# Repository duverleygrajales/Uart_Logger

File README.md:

No Longer Available
Only for Jekyll Probes
Install the jekyll theme in Docs Folder

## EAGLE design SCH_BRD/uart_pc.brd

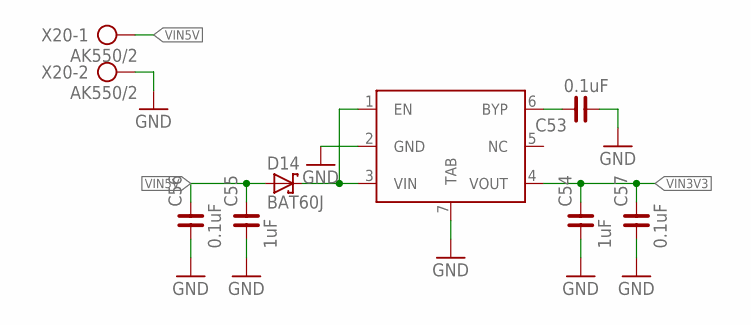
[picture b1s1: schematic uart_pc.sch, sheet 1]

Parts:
C53, C56, C57: 0.1uF; C0603
C54, C55: 1uF; C0603
D14: BAT60J; SOD323_ST
U$3: MIC5353-3.3YMT-TR; DFN-6_DC-L
X20: AK550/2

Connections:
GND: C53.1, C54.1, C55.1, C56.1, C57.1, U$3.2 (GND), U$3.7 (TAB), X20.2; also elsewhere on the board
unnamed: D14.C, U$3.1 (EN), U$3.3 (VIN)
unnamed: C53.2, U$3.6 (BYP)
VIN3V3: C54.2, C57.2, U$3.4 (VOUT); also elsewhere on the board
VIN5V: C55.2, C56.2, D14.A, X20.1; also elsewhere on the board

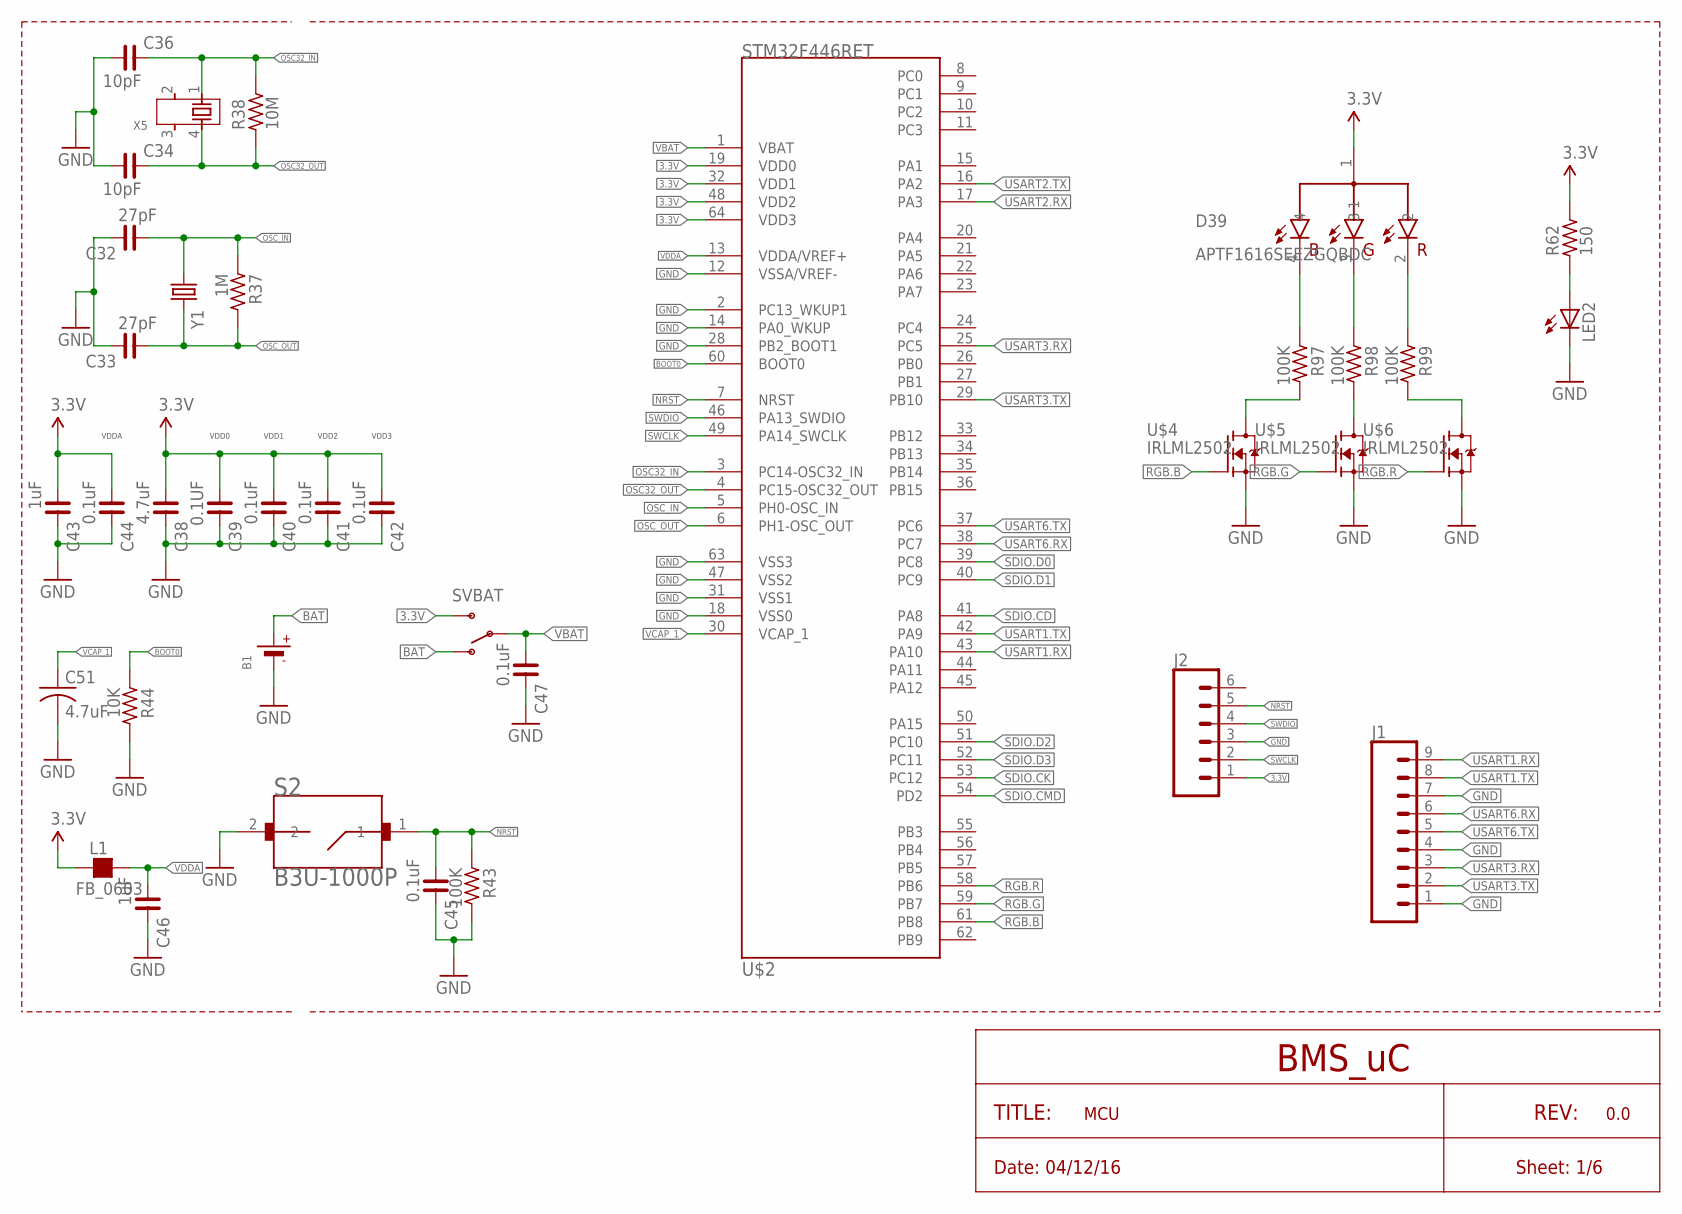
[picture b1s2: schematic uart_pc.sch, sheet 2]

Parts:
B1: BATTERYCR1220_SMT; CR1220
C32, C33: 27pF; C0603
C34, C36: 10pF; C0603
C38: 4.7uF; C0603
C39: 0.1UF; C0603
C40, C41, C42, C44, C45, C47: 0.1uF; C0603
C43, C46: 1uF; C0603
C51: 4.7uF; C1206
D39: APTF1616SEEZGQBDC; 0606(1616)
J1: CONN_09; 1X09
J2: CONN_06SILK_FEMALE_PTH; 1X06
L1: FB_0603; L0603
LED2: LEDCHIP-LED0603; CHIP-LED0603
R37: 1M; R0603
R38: 10M; R0603
R43, R97, R98, R99: 100K; R0603
R44: 10K; R0603
R62: 150; R0603
S2: B3U-1000P; SW_B3U-1000P
SVBAT: SWITCH-SPDTSMD; AYZ0202
U$2: STM32F446RET; LQFP64
U$4, U$5, U$6: IRLML2502; SOT23
X5: CRYSTAL-4PIN; ABRACON-ABS25-32.768KHZ
Y1: CRYSTALSMD; HC49UP

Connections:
3.3V: C38.1, C39.1, C40.1, C41.1, C42.1, C43.1, C44.1, D39.1, J2.1, L1.1, R62.2, SVBAT.3 (S), U$2.19 (VDD0), U$2.32 (VDD1), U$2.48 (VDD2), U$2.64 (VDD3); also elsewhere on the board
BAT: B1.+$1 (+), SVBAT.1 (O)
BOOT0: R44.1, U$2.60 (BOOT0)
GND: B1.-, C32.2, C33.2, C34.1, C36.1, C38.2, C39.2, C40.2, C41.2, C42.2, C43.2, C44.2, C45.2, C46.2, C47.2, C51.2, J1.1, J1.4, J1.7, J2.3, LED2.C, R43.2, R44.2, S2.2, U$2.2 (PC13_WKUP1), U$2.12 (VSSA/VREF-), U$2.14 (PA0_WKUP), U$2.18 (VSS0), U$2.28 (PB2_BOOT1), U$2.31 (VSS1), U$2.47 (VSS2), U$2.63 (VSS3), U$4.2 (S), U$5.2 (S), U$6.2 (S); also elsewhere on the board
unnamed: D39.3, R98.1
unnamed: D39.2, R99.1
unnamed: LED2.A, R62.1
unnamed: D39.4, R97.1
unnamed: R97.2, U$4.3 (D)
unnamed: R98.2, U$5.3 (D)
unnamed: R99.2, U$6.3 (D)
NRST: C45.1, J2.5, R43.1, S2.1, U$2.7 (NRST)
OSC32_IN: C36.2, R38.2, U$2.3 (PC14-OSC32_IN), X5.1
OSC32_OUT: C34.2, R38.1, U$2.4 (PC15-OSC32_OUT), X5.4
OSC_IN: C32.1, R37.1, U$2.5 (PH0-OSC_IN), Y1.1
OSC_OUT: C33.1, R37.2, U$2.6 (PH1-OSC_OUT), Y1.2
RGB.B: U$2.61 (PB8), U$4.1 (G)
RGB.G: U$2.59 (PB7), U$5.1 (G)
RGB.R: U$2.58 (PB6), U$6.1 (G)
SDIO.CD: U$2.41 (PA8); also elsewhere on the board
SDIO.CK: U$2.53 (PC12); also elsewhere on the board
SDIO.CMD: U$2.54 (PD2); also elsewhere on the board
SDIO.D0: U$2.39 (PC8); also elsewhere on the board
SDIO.D1: U$2.40 (PC9); also elsewhere on the board
SDIO.D2: U$2.51 (PC10); also elsewhere on the board
SDIO.D3: U$2.52 (PC11); also elsewhere on the board
SWCLK: J2.2, U$2.49 (PA14_SWCLK)
SWDIO: J2.4, U$2.46 (PA13_SWDIO)
USART1.RX: J1.9, U$2.43 (PA10)
USART1.TX: J1.8, U$2.42 (PA9)
USART2.RX: U$2.17 (PA3); also elsewhere on the board
USART2.TX: U$2.16 (PA2); also elsewhere on the board
USART3.RX: J1.3, U$2.25 (PC5)
USART3.TX: J1.2, U$2.29 (PB10)
USART6.RX: J1.6, U$2.38 (PC7)
USART6.TX: J1.5, U$2.37 (PC6)
VBAT: C47.1, SVBAT.2, U$2.1 (VBAT)
VCAP_1: C51.1, U$2.30 (VCAP_1)
VDDA: C46.1, L1.2, U$2.13 (VDDA/VREF+)

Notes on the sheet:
TITLE:
REV:
Sheet: 1/6
0.0
Date: 04/12/16
MCU
BMS_uC
VDD0
VDD1
VDD2
VDD3
VDDA

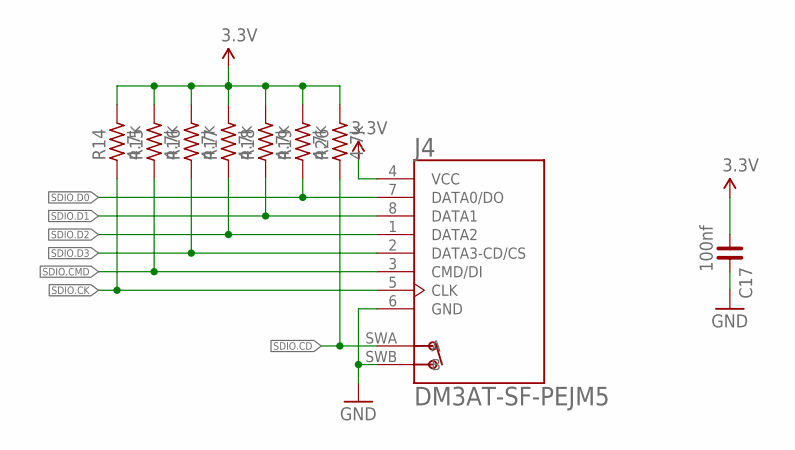
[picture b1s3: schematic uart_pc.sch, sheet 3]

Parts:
C17: 100nf; C0603
J4: DM3AT-SF-PEJM5; HRS_DM3AT-SF-PEJM5
R14, R15, R16, R17, R18, R19, R26: 4.7k; R0603

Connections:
3.3V: C17.1, J4.4 (VCC), R14.2, R15.2, R16.2, R17.2, R18.2, R19.2, R26.2; also elsewhere on the board
GND: C17.2, J4.6 (GND), J4.SWB (B); also elsewhere on the board
SDIO.CD: J4.SWA (A), R26.1; also elsewhere on the board
SDIO.CK: J4.5 (CLK), R14.1; also elsewhere on the board
SDIO.CMD: J4.3 (CMD/DI), R15.1; also elsewhere on the board
SDIO.D0: J4.7 (DATA0/DO), R19.1; also elsewhere on the board
SDIO.D1: J4.8 (DATA1), R18.1; also elsewhere on the board
SDIO.D2: J4.1 (DATA2), R17.1; also elsewhere on the board
SDIO.D3: J4.2 (DATA3-CD/CS), R16.1; also elsewhere on the board

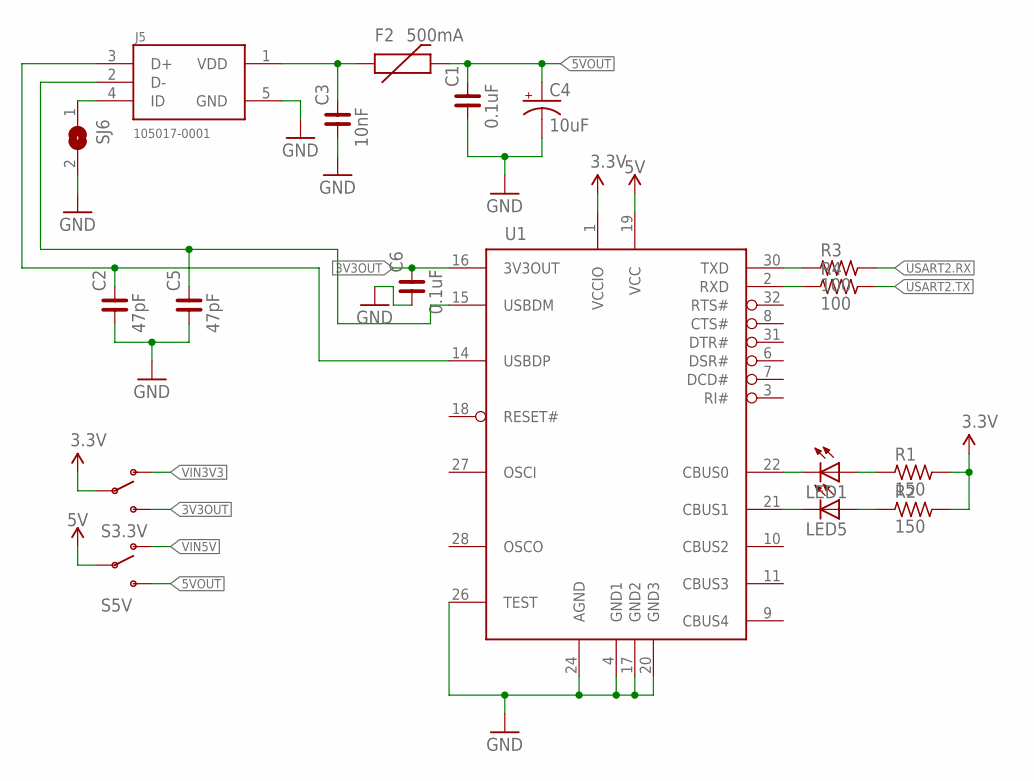
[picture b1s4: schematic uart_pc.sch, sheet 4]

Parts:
C1, C6: 0.1uF; C0603
C2, C5: 47pF; C0603
C3: 10nF; C0603
C4: 10uF; EIA3216
F2: 500mA; PTC-1206
J5: 105017-0001; MOLEX_105017-0001
LED1, LED5: LEDCHIPLED_0603; CHIPLED_0603
R1, R2: 150; R0603
R3, R4: 100; R0603
S3.3V, S5V: SWITCH-SPDTSMD; AYZ0202
SJ6: SOLDERJUMPER; SOLDERJUMPER_ARROW_NOPASTE
U1: FT232RQ; LQFP32

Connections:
3.3V: R1.2, R2.2, S3.3V.2, U1.1 (VCCIO); also elsewhere on the board
3V3OUT: C6.2, S3.3V.3 (S), U1.16 (3V3OUT)
5V: S5V.2, U1.19 (VCC)
5VOUT: C1.2, C4.A (+), F2.2, S5V.3 (S)
GND: C1.1, C2.1, C3.1, C4.C (-), C5.1, C6.1, J5.5 (GND), SJ6.2, U1.4 (GND1), U1.17 (GND2), U1.20 (GND3), U1.24 (AGND), U1.26 (TEST); also elsewhere on the board
unnamed: C5.2, J5.2 (D-), U1.15 (USBDM)
unnamed: C2.2, J5.3 (D+), U1.14 (USBDP)
unnamed: C3.2, F2.1, J5.1 (VDD)
unnamed: J5.4 (ID), SJ6.1
unnamed: LED1.C, U1.22 (CBUS0)
unnamed: LED5.C, U1.21 (CBUS1)
unnamed: LED1.A, R1.1
unnamed: LED5.A, R2.1
unnamed: R3.1, U1.30 (TXD)
unnamed: R4.1, U1.2 (RXD)
USART2.RX: R3.2; also elsewhere on the board
USART2.TX: R4.2; also elsewhere on the board
VIN3V3: S3.3V.1 (O); also elsewhere on the board
VIN5V: S5V.1 (O); also elsewhere on the board

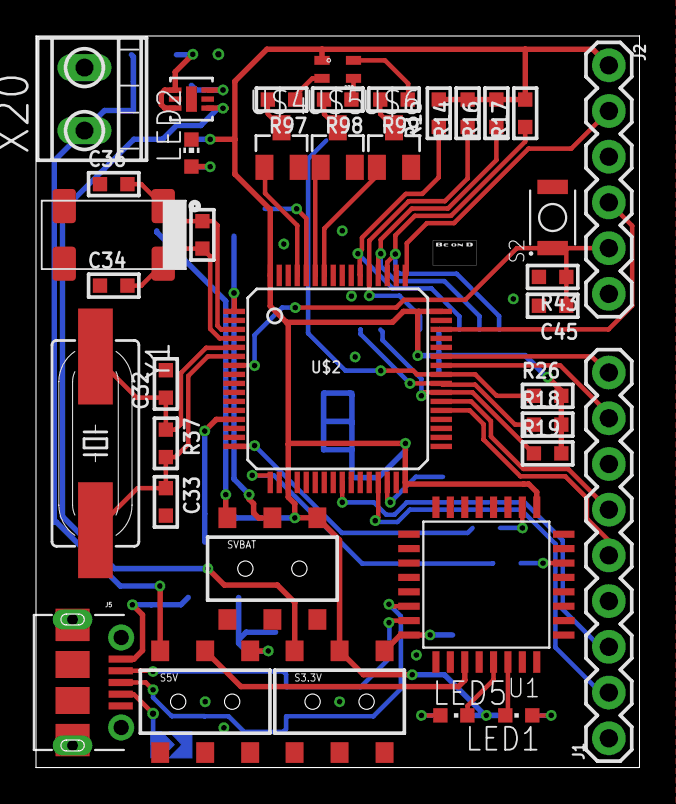
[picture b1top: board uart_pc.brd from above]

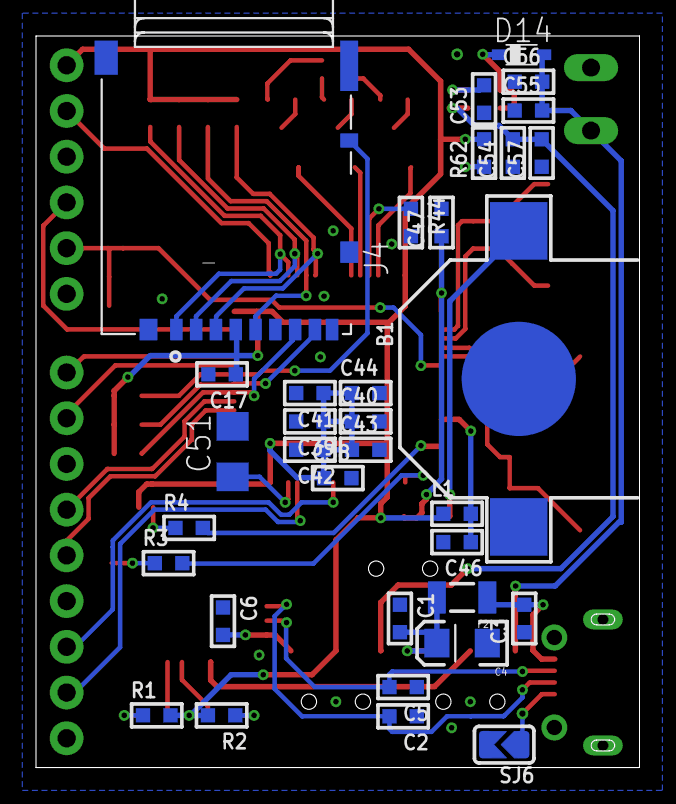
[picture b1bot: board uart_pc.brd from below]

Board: 2 copper layers, 33.5 x 40.6 mm, 72 parts (34 on the bottom side), 56 nets.

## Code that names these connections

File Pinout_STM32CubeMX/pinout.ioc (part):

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Mcu.Name=STM32F446R(C-E)Tx
Mcu.Package=LQFP64
Mcu.UserName=STM32F446RETx
PA10.Mode=Asynchronous
PA10.Signal=USART1_RX
PA2.Mode=Asynchronous
PA2.Signal=USART2_TX
PA3.Mode=Asynchronous
PA3.Signal=USART2_RX
PA8.GPIOParameters=GPIO_Label
PA8.GPIO_Label=Card_Detect
PA8.Signal=GPIO_Input
PA9.Mode=Asynchronous
PA9.Signal=USART1_TX
PB10.Mode=Asynchronous
PB10.Signal=USART3_TX
PB6.Signal=S_TIM4_CH1
PB7.Signal=S_TIM4_CH2
PB8.Signal=S_TIM4_CH3
PC10.Mode=SD_4_bits_Wide_bus
PC10.Signal=SDIO_D2
PC11.Mode=SD_4_bits_Wide_bus
PC11.Signal=SDIO_D3
PC12.Mode=SD_4_bits_Wide_bus
PC12.Signal=SDIO_CK
PC14-OSC32_IN.Mode=LSE-External-Oscillator
PC14-OSC32_IN.Signal=RCC_OSC32_IN
PC15-OSC32_OUT.Mode=LSE-External-Oscillator
PC15-OSC32_OUT.Signal=RCC_OSC32_OUT
PC5.Mode=Asynchronous
PC5.Signal=USART3_RX
PC6.Mode=Asynchronous
PC6.Signal=USART6_TX
PC7.Mode=Asynchronous
PC7.Signal=USART6_RX
PC8.Mode=SD_4_bits_Wide_bus
PC8.Signal=SDIO_D0
PC9.Mode=SD_4_bits_Wide_bus
PC9.Signal=SDIO_D1
PD2.Mode=SD_4_bits_Wide_bus
PD2.Signal=SDIO_CMD
PH0-OSC_IN.Mode=HSE-External-Oscillator
PH0-OSC_IN.Signal=RCC_OSC_IN
PH1-OSC_OUT.Mode=HSE-External-Oscillator
PH1-OSC_OUT.Signal=RCC_OSC_OUT
RCC.HSE_VALUE=8000000
RCC.SYSCLKFreq_VALUE=72000000
RCC.SYSCLKSource=RCC_SYSCLKSOURCE_PLLCLK

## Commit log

2017-09-19 ToDo .brd
    Full .sch we need to finish the board
2017-09-19 Work .brd 19/09/17
2017-09-20 Work .brd 20/09/17
2017-09-21 Finished sch and brd
    Version beta
2018-03-28 Something to commit
2018-03-28 Readme Change
2018-04-01 algo
2018-04-03 create docs folder into master
2018-04-03 Set theme jekyll-theme-slate
2018-04-03 add branch
2018-04-03 added theme to Gemfile & _config.yml
2018-04-03 Add slate theme to Repo in gh-pages branch

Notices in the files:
parts and their libraries:
microbuilder: This work is placed in the public domain, and may be freely used for commercial and non-commercial work with the following conditions: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
rc-master-smd: Copyright (C) 2007, Bob Starr
